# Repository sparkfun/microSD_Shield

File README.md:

SparkFun microSD Shield
===========================

[*microSD Shield (DEV-12761)*](https://www.sparkfun.com/products/12761)

The microSD shield equips your Arduino with mass-storage capability, so you can use it for data-logging or other related projects. 

Repository Contents
-------------------

* **/Firmware** - Example .INO sketch for Arduino. Requires the SD.h library
* **/Hardware** - All Eagle design files (.brd, .sch)
* **/Production** - Test bed files and production panel files

Documentation
--------------
* **[Hookup Guide](https://learn.sparkfun.com/tutorials/microsd-shield-and-sd-breakout-hookup-guide)** - Basic hookup guide for the microSD Shield.
* **[SparkFun Fritzing repo](https://github.com/sparkfun/Fritzing_Parts)** - Fritzing diagrams for SparkFun products.
* **[SparkFun 3D Model repo](https://github.com/sparkfun/3D_Models)** - 3D models of SparkFun products. 

Product Versions
----------------
* [DEV-09802](https://www.sparkfun.com/products/9802)- Hardware version 1.3. Designed for Uno (not R3)

Version History
---------------
* [v1.3](https://github.com/sparkfun/microSD_Shield/tree/V_1.3) Version 1.3

License Information
-------------------

This product is _**open source**_! 

Please review the LICENSE.md file for license information. 

If you have any questions or concerns on licensing, please contact techsupport@sparkfun.com.

Distributed as-is; no warranty is given.

- Your friends at SparkFun.

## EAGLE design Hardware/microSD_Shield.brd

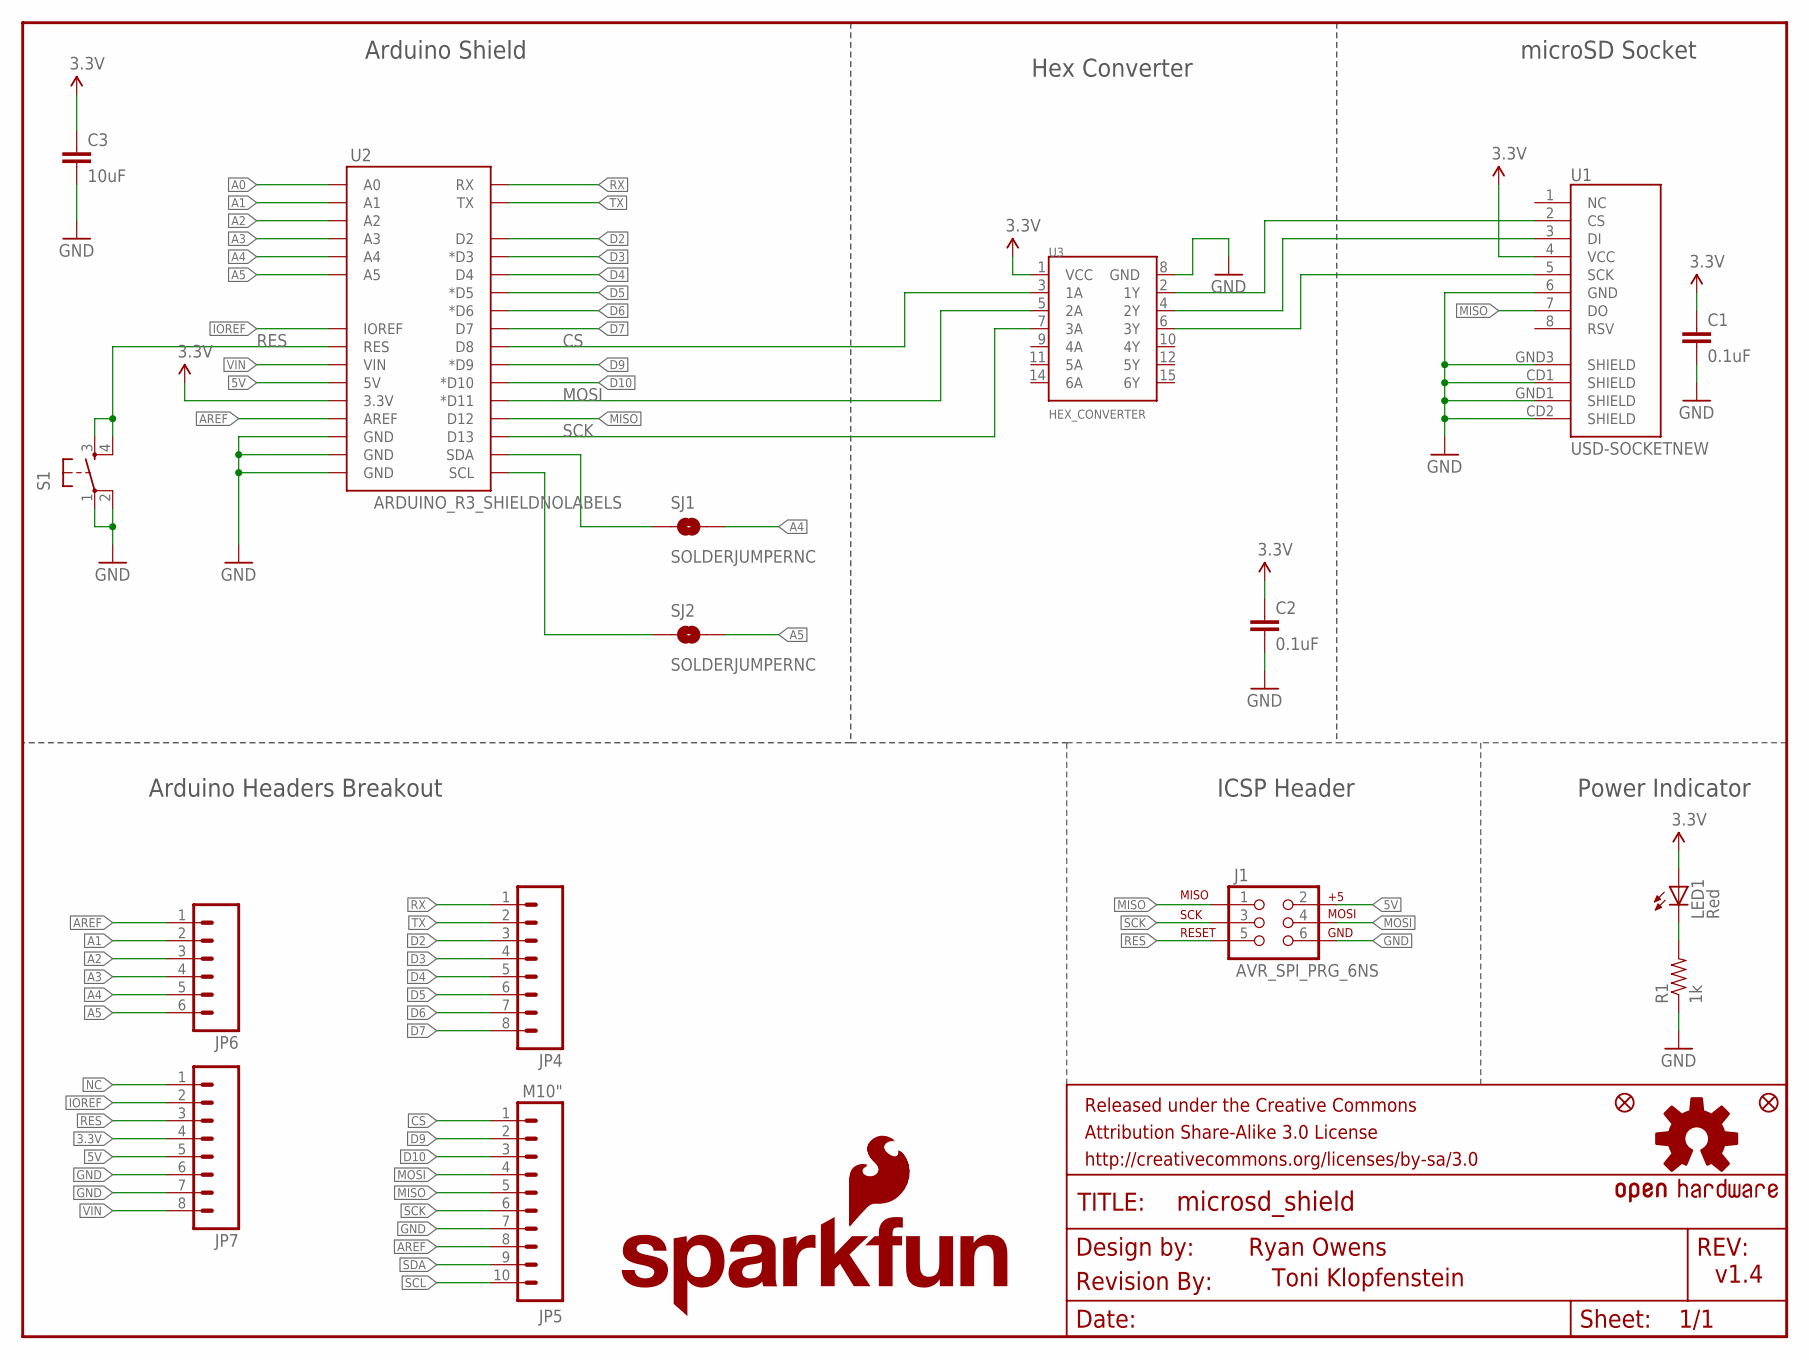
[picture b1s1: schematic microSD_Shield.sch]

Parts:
C1, C2: 0.1uF; 0603-CAP
C3: 10uF; 0603-CAP
FRAME1: FRAME-LETTER; CREATIVE_COMMONS
J1: AVR_SPI_PRG_6NS; 2X3-NS
JP1: SFE_LOGO_NAME_FLAME.1_INCH; SFE_LOGO_NAME_FLAME_.1
JP2, JP3: FIDUCIAL1X2; FIDUCIAL-1X2
JP4: M08; 1X08
JP5: M10"; 1X10
JP6: M06SIP; 1X06
JP7: M081X08; 1X08
LED1: Red; LED-0603
LOGO1: OSHW-LOGOM; OSHW-LOGO-M
LOGO2: SFE_LOGO_FLAME.6_INCH; SFE_LOGO_FLAME_.6
R1: 1k; 0603-RES
S1: TAC_SWITCHSMD; TACTILE_SWITCH_SMD
SJ1, SJ2: SOLDERJUMPERNC; SJ_2S
U1: USD-SOCKETNEW; MICRO-SD-SOCKET-PP
U2: ARDUINO_R3_SHIELDNOLABELS; UNO_R3_SHIELD_NOLABELS
U3: HEX_CONVERTER; SO016
U$1: REVISION

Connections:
3.3V: C1.1, C2.1, C3.1, JP7.4, LED1.A, U1.4 (VCC), U2.3.3V, U3.1 (VCC)
5V: J1.2, JP7.5, U2.5V
A0: JP6.1, U2.A0
A1: JP6.2, U2.A1
A2: JP6.3, U2.A2
A3: JP6.4, U2.A3
A4: JP6.5, SJ1.2, U2.A4
A5: JP6.6, SJ2.2, U2.A5
AREF: JP5.8, U2.AREF
CS: JP5.1, U2.D8, U3.3 (1A)
D2: JP4.3, U2.D2
D3: JP4.4, U2.D3 (*D3)
D4: JP4.5, U2.D4
D5: JP4.6, U2.D5 (*D5)
D6: JP4.7, U2.D6 (*D6)
D7: JP4.8, U2.D7
D9: JP5.2, U2.D9 (*D9)
D10: JP5.3, U2.D10 (*D10)
GND: C1.2, C2.2, C3.2, J1.6, JP5.7, JP7.6, JP7.7, R1.1, S1.1, S1.2, U1.6 (GND), U1.CD1 (SHIELD), U1.CD2 (SHIELD), U1.GND1 (SHIELD), U1.GND3 (SHIELD), U2.GND@0 (GND), U2.GND@1 (GND), U2.GND@2 (GND), U3.8 (GND)
IOREF: JP7.2, U2.IOREF
MISO: J1.1, JP5.5, U1.7 (DO), U2.D12
MOSI: J1.4, JP5.4, U2.D11 (*D11), U3.5 (2A)
unnamed: U1.3 (DI), U3.4 (2Y)
unnamed: U1.5 (SCK), U3.6 (3Y)
unnamed: LED1.C, R1.2
unnamed: U1.2 (CS), U3.2 (1Y)
NC: JP7.1
RES: J1.5, JP7.3, S1.3, S1.4, U2.RES
RX: JP4.1, U2.RX
SCK: J1.3, JP5.6, U2.D13, U3.7 (3A)
SCL: JP5.10, SJ2.1, U2.SCL
SDA: JP5.9, SJ1.1, U2.SDA
TX: JP4.2, U2.TX
VIN: JP7.8, U2.VIN

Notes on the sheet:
Power Indicator
Ryan Owens
v1.4
Toni Klopfenstein
Arduino Headers Breakout
ICSP Header
microSD Socket
Hex Converter
Arduino Shield

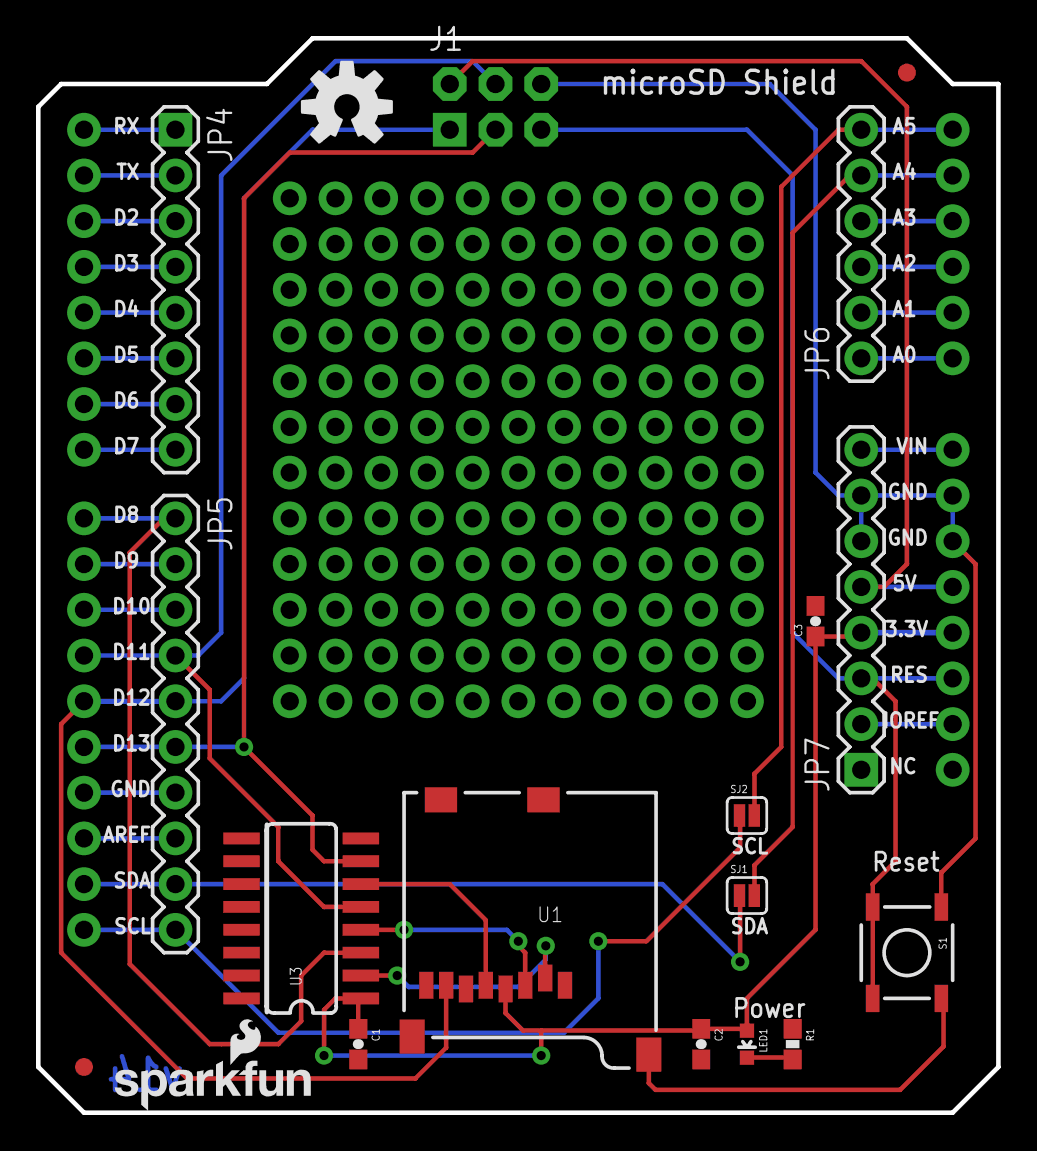
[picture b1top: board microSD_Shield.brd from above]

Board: 2 copper layers, 53.3 x 59.7 mm, 23 parts (1 on the bottom side), 33 nets.

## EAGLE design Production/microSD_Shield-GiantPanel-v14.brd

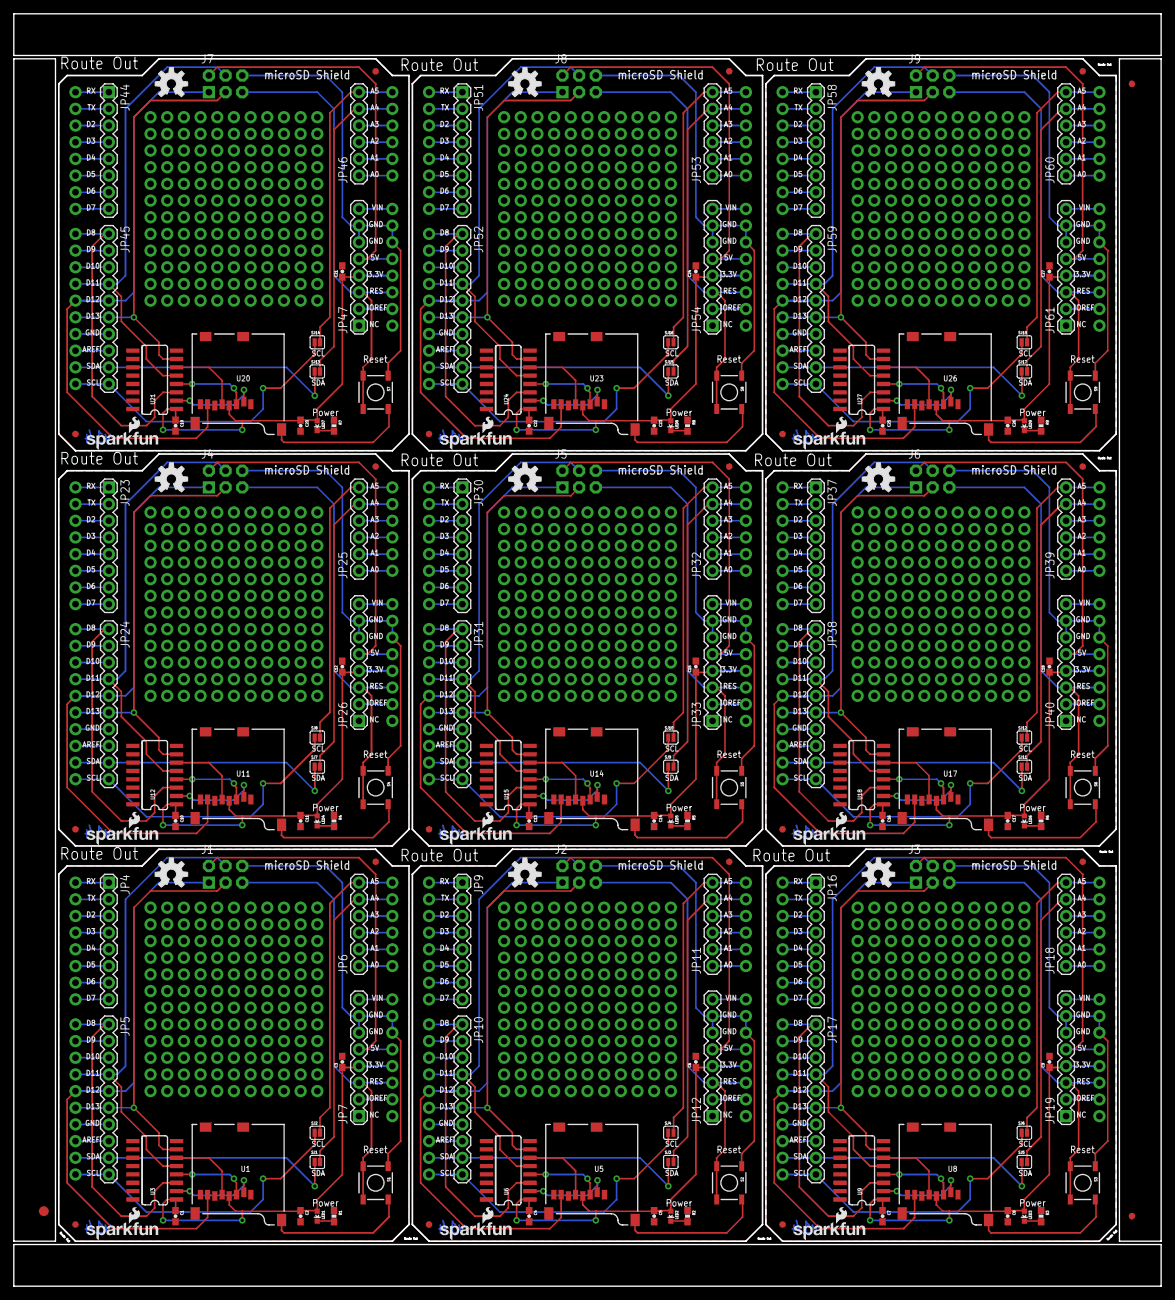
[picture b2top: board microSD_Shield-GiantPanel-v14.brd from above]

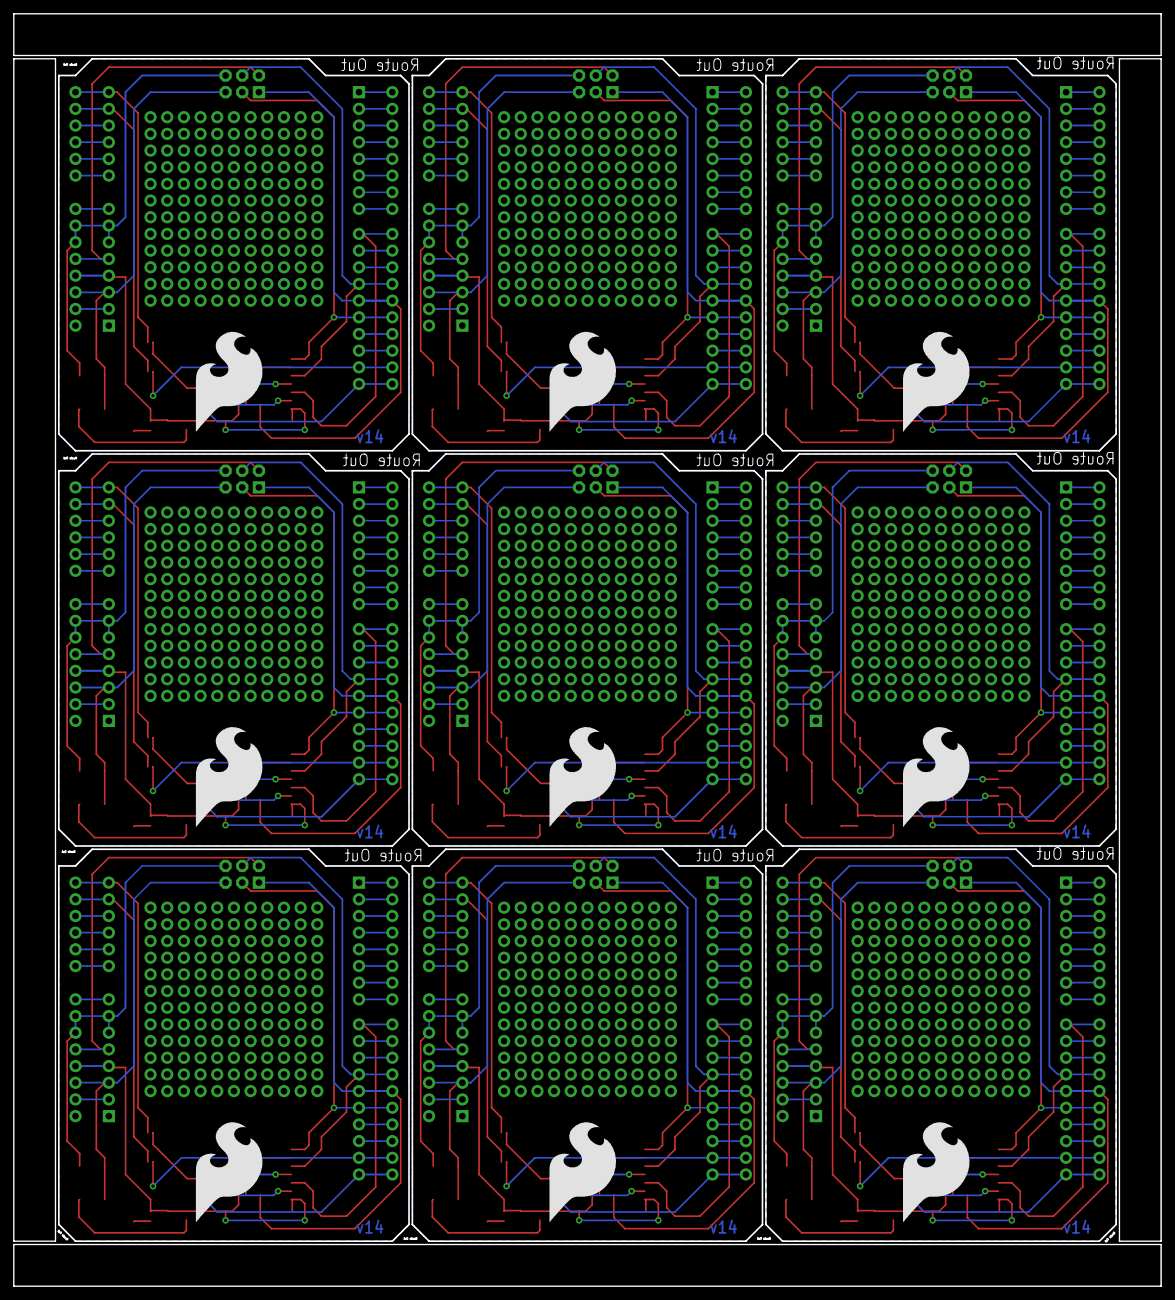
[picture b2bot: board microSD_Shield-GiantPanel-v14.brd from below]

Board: 2 copper layers, 174.8 x 193.8 mm, 192 parts (9 on the bottom side), 297 nets.

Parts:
C1, C2, C4, C5, C7, C8, C10, C11, C13, C14, C16, C17, C19, C20, C22, C23, C25, C26: 0.1uF; 0603-CAP
C3, C6, C9, C12, C15, C18, C21, C24, C27: 10uF; 0603-CAP
E$1: FIDUCIAL-1.5X3
E$6, E$8: FIDUCIAL-1X2
J1, J2, J3, J4, J5, J6, J7, J8, J9: AVR_SPI_PRG_6NS; 2X3-NS
JP1, JP8, JP15, JP22, JP29, JP36, JP43, JP50, JP57: SFE_LOGO_NAME_FLAME.1_INCH; SFE_LOGO_NAME_FLAME_.1
JP2, JP3, JP13, JP14, JP20, JP21, JP27, JP28, JP34, JP35, JP41, JP42, JP48, JP49, JP55, JP56, JP62, JP63: FIDUCIAL1X2; FIDUCIAL-1X2
JP4, JP7, JP9, JP12, JP16, JP19, JP23, JP26, JP30, JP33, JP37, JP40, JP44, JP47, JP51, JP54, JP58, JP61: 1X08
JP5, JP10, JP17, JP24, JP31, JP38, JP45, JP52, JP59: M10"; 1X10
JP6, JP11, JP18, JP25, JP32, JP39, JP46, JP53, JP60: 1X06
LED1, LED2, LED3, LED4, LED5, LED6, LED7, LED8, LED9: Red; LED-0603
LOGO1, LOGO3, LOGO5, LOGO7, LOGO9, LOGO11, LOGO13, LOGO15, LOGO17: OSHW-LOGOM; OSHW-LOGO-M
LOGO2, LOGO4, LOGO6, LOGO8, LOGO10, LOGO12, LOGO14, LOGO16, LOGO18: SFE_LOGO_FLAME.6_INCH; SFE_LOGO_FLAME_.6
R1, R2, R3, R4, R5, R6, R7, R8, R9: 1k; 0603-RES
S1, S2, S3, S4, S5, S6, S7, S8, S9: TACTILE_SWITCH_SMD
SJ1, SJ2, SJ3, SJ4, SJ5, SJ6, SJ7, SJ8, SJ9, SJ10, SJ11, SJ12, SJ13, SJ14, SJ15, SJ16, SJ17, SJ18: SOLDERJUMPERNC; SJ_2S
U1, U5, U8, U11, U14, U17, U20, U23, U26: USD-SOCKETNEW; MICRO-SD-SOCKET-PP
U2, U4, U7, U10, U13, U16, U19, U22, U25: ARDUINO_R3_SHIELDNOLABELS; UNO_R3_SHIELD_NOLABELS
U3, U6, U9, U12, U15, U18, U21, U24, U27: HEX_CONVERTER; SO016

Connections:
3.3V: C1.1, C2.1, C3.1, JP7.4, LED1.A, U1.4, U2.3.3V, U3.1
3.3V1: C4.1, C5.1, C6.1, JP12.4, LED2.A, U4.3.3V, U5.4, U6.1
3.3V2: C7.1, C8.1, C9.1, JP19.4, LED3.A, U7.3.3V, U8.4, U9.1
3.3V3: C10.1, C11.1, C12.1, JP26.4, LED4.A, U10.3.3V, U11.4, U12.1
3.3V4: C13.1, C14.1, C15.1, JP33.4, LED5.A, U13.3.3V, U14.4, U15.1
3.3V5: C16.1, C17.1, C18.1, JP40.4, LED6.A, U16.3.3V, U17.4, U18.1
3.3V6: C19.1, C20.1, C21.1, JP47.4, LED7.A, U19.3.3V, U20.4, U21.1
3.3V7: C22.1, C23.1, C24.1, JP54.4, LED8.A, U22.3.3V, U23.4, U24.1
3.3V8: C25.1, C26.1, C27.1, JP61.4, LED9.A, U25.3.3V, U26.4, U27.1
5V: J1.2, JP7.5, U2.5V
5V1: J2.2, JP12.5, U4.5V
5V2: J3.2, JP19.5, U7.5V
5V3: J4.2, JP26.5, U10.5V
5V4: J5.2, JP33.5, U13.5V
5V5: J6.2, JP40.5, U16.5V
5V6: J7.2, JP47.5, U19.5V
5V7: J8.2, JP54.5, U22.5V
5V8: J9.2, JP61.5, U25.5V
A0: JP6.1, U2.A0
A1: JP6.2, U2.A1
A2: JP6.3, U2.A2
A3: JP6.4, U2.A3
A4: JP6.5, SJ1.2, U2.A4
A5: JP6.6, SJ2.2, U2.A5
A6: JP11.1, U4.A0
A7: JP11.2, U4.A1
A8: JP11.3, U4.A2
A9: JP11.4, U4.A3
A10: JP11.5, SJ3.2, U4.A4
A11: JP11.6, SJ4.2, U4.A5
A12: JP18.1, U7.A0
A13: JP18.2, U7.A1
A14: JP18.3, U7.A2
A15: JP18.4, U7.A3
A16: JP18.5, SJ5.2, U7.A4
A17: JP18.6, SJ6.2, U7.A5
A18: JP25.1, U10.A0
A19: JP25.2, U10.A1
A20: JP25.3, U10.A2
A21: JP25.4, U10.A3
A22: JP25.5, SJ7.2, U10.A4
A23: JP25.6, SJ8.2, U10.A5
A24: JP32.1, U13.A0
A25: JP32.2, U13.A1
A26: JP32.3, U13.A2
A27: JP32.4, U13.A3
A28: JP32.5, SJ9.2, U13.A4
A29: JP32.6, SJ10.2, U13.A5
A30: JP39.1, U16.A0
A31: JP39.2, U16.A1
A32: JP39.3, U16.A2
A33: JP39.4, U16.A3
A34: JP39.5, SJ11.2, U16.A4
A35: JP39.6, SJ12.2, U16.A5
A36: JP46.1, U19.A0
A37: JP46.2, U19.A1
A38: JP46.3, U19.A2
A39: JP46.4, U19.A3
A40: JP46.5, SJ13.2, U19.A4
A41: JP46.6, SJ14.2, U19.A5
A42: JP53.1, U22.A0
A43: JP53.2, U22.A1
A44: JP53.3, U22.A2
A45: JP53.4, U22.A3
A46: JP53.5, SJ15.2, U22.A4
A47: JP53.6, SJ16.2, U22.A5
A48: JP60.1, U25.A0
A49: JP60.2, U25.A1
A50: JP60.3, U25.A2
A51: JP60.4, U25.A3
A52: JP60.5, SJ17.2, U25.A4
A53: JP60.6, SJ18.2, U25.A5
AREF: JP5.8, U2.AREF
AREF1: JP10.8, U4.AREF
AREF2: JP17.8, U7.AREF
AREF3: JP24.8, U10.AREF
AREF4: JP31.8, U13.AREF
AREF5: JP38.8, U16.AREF
AREF6: JP45.8, U19.AREF
AREF7: JP52.8, U22.AREF
AREF8: JP59.8, U25.AREF
CS: JP5.1, U2.D8, U3.3
CS1: JP10.1, U4.D8, U6.3
CS2: JP17.1, U7.D8, U9.3
CS3: JP24.1, U10.D8, U12.3
CS4: JP31.1, U13.D8, U15.3
CS5: JP38.1, U16.D8, U18.3
CS6: JP45.1, U19.D8, U21.3
CS7: JP52.1, U22.D8, U24.3
CS8: JP59.1, U25.D8, U27.3
D1: JP9.3, U4.D2
D2: JP4.3, U2.D2
D3: JP4.4, U2.D3
D4: JP4.5, U2.D4
D5: JP4.6, U2.D5
D6: JP4.7, U2.D6
D7: JP4.8, U2.D7
D8: JP9.4, U4.D3
D9: JP5.2, U2.D9
D10: JP5.3, U2.D10
D11: JP9.5, U4.D4
D12: JP9.6, U4.D5
D13: JP9.7, U4.D6
D14: JP9.8, U4.D7
D15: JP10.2, U4.D9
D16: JP10.3, U4.D10
D17: JP16.3, U7.D2
D18: JP16.4, U7.D3
D19: JP16.5, U7.D4
D20: JP16.6, U7.D5
D21: JP16.7, U7.D6
D22: JP16.8, U7.D7
D23: JP17.2, U7.D9
D24: JP17.3, U7.D10
D25: JP23.3, U10.D2
D26: JP23.4, U10.D3
D27: JP23.5, U10.D4
D28: JP23.6, U10.D5
D29: JP23.7, U10.D6
D30: JP23.8, U10.D7
D31: JP24.2, U10.D9
D32: JP24.3, U10.D10
D33: JP30.3, U13.D2
D34: JP30.4, U13.D3
D35: JP30.5, U13.D4
D36: JP30.6, U13.D5
D37: JP30.7, U13.D6
D38: JP30.8, U13.D7
D39: JP31.2, U13.D9
D40: JP31.3, U13.D10
D41: JP37.3, U16.D2
D42: JP37.4, U16.D3
D43: JP37.5, U16.D4
D44: JP37.6, U16.D5
D45: JP37.7, U16.D6
D46: JP37.8, U16.D7
D47: JP38.2, U16.D9
D48: JP38.3, U16.D10
D49: JP44.3, U19.D2
D50: JP44.4, U19.D3
D51: JP44.5, U19.D4
D52: JP44.6, U19.D5
D53: JP44.7, U19.D6
D54: JP44.8, U19.D7
D55: JP45.2, U19.D9
D56: JP45.3, U19.D10
D57: JP51.3, U22.D2
D58: JP51.4, U22.D3
D59: JP51.5, U22.D4
D60: JP51.6, U22.D5
D61: JP51.7, U22.D6
D62: JP51.8, U22.D7
D63: JP52.2, U22.D9
D64: JP52.3, U22.D10
D65: JP58.3, U25.D2
D66: JP58.4, U25.D3
D67: JP58.5, U25.D4
D68: JP58.6, U25.D5
D69: JP58.7, U25.D6
D70: JP58.8, U25.D7
D71: JP59.2, U25.D9
D72: JP59.3, U25.D10
GND: C1.2, C2.2, C3.2, J1.6, JP5.7, JP7.6, JP7.7, R1.1, S1.1, S1.2, U1.6, U1.CD1, U1.CD2, U1.GND1, U1.GND3, U2.GND@0, U2.GND@1, U2.GND@2, U3.8
GND1: C4.2, C5.2, C6.2, J2.6, JP10.7, JP12.6, JP12.7, R2.1, S2.1, S2.2, U4.GND@0, U4.GND@1, U4.GND@2, U5.6, U5.CD1, U5.CD2, U5.GND1, U5.GND3, U6.8
GND2: C7.2, C8.2, C9.2, J3.6, JP17.7, JP19.6, JP19.7, R3.1, S3.1, S3.2, U7.GND@0, U7.GND@1, U7.GND@2, U8.6, U8.CD1, U8.CD2, U8.GND1, U8.GND3, U9.8
GND3: C10.2, C11.2, C12.2, J4.6, JP24.7, JP26.6, JP26.7, R4.1, S4.1, S4.2, U10.GND@0, U10.GND@1, U10.GND@2, U11.6, U11.CD1, U11.CD2, U11.GND1, U11.GND3, U12.8
GND4: C13.2, C14.2, C15.2, J5.6, JP31.7, JP33.6, JP33.7, R5.1, S5.1, S5.2, U13.GND@0, U13.GND@1, U13.GND@2, U14.6, U14.CD1, U14.CD2, U14.GND1, U14.GND3, U15.8
GND5: C16.2, C17.2, C18.2, J6.6, JP38.7, JP40.6, JP40.7, R6.1, S6.1, S6.2, U16.GND@0, U16.GND@1, U16.GND@2, U17.6, U17.CD1, U17.CD2, U17.GND1, U17.GND3, U18.8
GND6: C19.2, C20.2, C21.2, J7.6, JP45.7, JP47.6, JP47.7, R7.1, S7.1, S7.2, U19.GND@0, U19.GND@1, U19.GND@2, U20.6, U20.CD1, U20.CD2, U20.GND1, U20.GND3, U21.8
GND7: C22.2, C23.2, C24.2, J8.6, JP52.7, JP54.6, JP54.7, R8.1, S8.1, S8.2, U22.GND@0, U22.GND@1, U22.GND@2, U23.6, U23.CD1, U23.CD2, U23.GND1, U23.GND3, U24.8
GND8: C25.2, C26.2, C27.2, J9.6, JP59.7, JP61.6, JP61.7, R9.1, S9.1, S9.2, U25.GND@0, U25.GND@1, U25.GND@2, U26.6, U26.CD1, U26.CD2, U26.GND1, U26.GND3, U27.8
IOREF: JP7.2, U2.IOREF
IOREF1: JP12.2, U4.IOREF
IOREF2: JP19.2, U7.IOREF
IOREF3: JP26.2, U10.IOREF
IOREF4: JP33.2, U13.IOREF
IOREF5: JP40.2, U16.IOREF
IOREF6: JP47.2, U19.IOREF
IOREF7: JP54.2, U22.IOREF
IOREF8: JP61.2, U25.IOREF
MISO: J1.1, JP5.5, U1.7, U2.D12
MISO1: J2.1, JP10.5, U4.D12, U5.7
MISO2: J3.1, JP17.5, U7.D12, U8.7
MISO3: J4.1, JP24.5, U10.D12, U11.7
MISO4: J5.1, JP31.5, U13.D12, U14.7
MISO5: J6.1, JP38.5, U16.D12, U17.7
MISO6: J7.1, JP45.5, U19.D12, U20.7
MISO7: J8.1, JP52.5, U22.D12, U23.7
MISO8: J9.1, JP59.5, U25.D12, U26.7
MOSI: J1.4, JP5.4, U2.D11, U3.5
MOSI1: J2.4, JP10.4, U4.D11, U6.5
MOSI2: J3.4, JP17.4, U7.D11, U9.5
MOSI3: J4.4, JP24.4, U10.D11, U12.5
MOSI4: J5.4, JP31.4, U13.D11, U15.5
MOSI5: J6.4, JP38.4, U16.D11, U18.5
MOSI6: J7.4, JP45.4, U19.D11, U21.5
MOSI7: J8.4, JP52.4, U22.D11, U24.5
MOSI8: J9.4, JP59.4, U25.D11, U27.5
unnamed: U5.3, U6.4
unnamed: U1.3, U3.4
unnamed: LED2.C, R2.2
unnamed: U1.5, U3.6
unnamed: LED1.C, R1.2
unnamed: U1.2, U3.2
unnamed: U5.2, U6.2
unnamed: U5.5, U6.6
unnamed: U8.3, U9.4
unnamed: LED3.C, R3.2
unnamed: U8.2, U9.2
unnamed: U8.5, U9.6
unnamed: U11.3, U12.4
unnamed: LED4.C, R4.2
unnamed: U11.2, U12.2
unnamed: U11.5, U12.6
unnamed: U14.3, U15.4
unnamed: LED5.C, R5.2
unnamed: U14.2, U15.2
unnamed: U14.5, U15.6
unnamed: U17.3, U18.4
unnamed: LED6.C, R6.2
unnamed: U17.2, U18.2
unnamed: U17.5, U18.6
unnamed: U20.3, U21.4
unnamed: LED7.C, R7.2
unnamed: U20.2, U21.2
unnamed: U20.5, U21.6
unnamed: U23.3, U24.4
unnamed: LED8.C, R8.2
unnamed: U23.2, U24.2
unnamed: U23.5, U24.6
unnamed: U26.3, U27.4
unnamed: LED9.C, R9.2
unnamed: U26.2, U27.2
unnamed: U26.5, U27.6
RES: J1.5, JP7.3, S1.3, S1.4, U2.RES
RES1: J2.5, JP12.3, S2.3, S2.4, U4.RES
RES2: J3.5, JP19.3, S3.3, S3.4, U7.RES
RES3: J4.5, JP26.3, S4.3, S4.4, U10.RES
RES4: J5.5, JP33.3, S5.3, S5.4, U13.RES
RES5: J6.5, JP40.3, S6.3, S6.4, U16.RES
RES6: J7.5, JP47.3, S7.3, S7.4, U19.RES
RES7: J8.5, JP54.3, S8.3, S8.4, U22.RES
RES8: J9.5, JP61.3, S9.3, S9.4, U25.RES
RX: JP4.1, U2.RX
RX1: JP9.1, U4.RX
RX2: JP16.1, U7.RX
RX3: JP23.1, U10.RX
RX4: JP30.1, U13.RX
RX5: JP37.1, U16.RX
RX6: JP44.1, U19.RX
RX7: JP51.1, U22.RX
RX8: JP58.1, U25.RX
SCK: J1.3, JP5.6, U2.D13, U3.7
SCK1: J2.3, JP10.6, U4.D13, U6.7
SCK2: J3.3, JP17.6, U7.D13, U9.7
SCK3: J4.3, JP24.6, U10.D13, U12.7
SCK4: J5.3, JP31.6, U13.D13, U15.7
SCK5: J6.3, JP38.6, U16.D13, U18.7
SCK6: J7.3, JP45.6, U19.D13, U21.7
SCK7: J8.3, JP52.6, U22.D13, U24.7
SCK8: J9.3, JP59.6, U25.D13, U27.7
SCL: JP5.10, SJ2.1, U2.SCL
SCL1: JP10.10, SJ4.1, U4.SCL
SCL2: JP17.10, SJ6.1, U7.SCL
SCL3: JP24.10, SJ8.1, U10.SCL
SCL4: JP31.10, SJ10.1, U13.SCL
SCL5: JP38.10, SJ12.1, U16.SCL
SCL6: JP45.10, SJ14.1, U19.SCL
SCL7: JP52.10, SJ16.1, U22.SCL
SCL8: JP59.10, SJ18.1, U25.SCL
SDA: JP5.9, SJ1.1, U2.SDA
SDA1: JP10.9, SJ3.1, U4.SDA
SDA2: JP17.9, SJ5.1, U7.SDA
SDA3: JP24.9, SJ7.1, U10.SDA
SDA4: JP31.9, SJ9.1, U13.SDA
SDA5: JP38.9, SJ11.1, U16.SDA
SDA6: JP45.9, SJ13.1, U19.SDA
SDA7: JP52.9, SJ15.1, U22.SDA
SDA8: JP59.9, SJ17.1, U25.SDA
TX: JP4.2, U2.TX
TX1: JP9.2, U4.TX
TX2: JP16.2, U7.TX
TX3: JP23.2, U10.TX
TX4: JP30.2, U13.TX
TX5: JP37.2, U16.TX
TX6: JP44.2, U19.TX
TX7: JP51.2, U22.TX
TX8: JP58.2, U25.TX
VIN: JP7.8, U2.VIN
VIN1: JP12.8, U4.VIN
VIN2: JP19.8, U7.VIN
VIN3: JP26.8, U10.VIN
VIN4: JP33.8, U13.VIN
VIN5: JP40.8, U16.VIN
VIN6: JP47.8, U19.VIN
VIN7: JP54.8, U22.VIN
VIN8: JP61.8, U25.VIN

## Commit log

2014-02-11 Initial board file commit
2014-02-12 Adding v1.4 board files
2014-02-25 Adding decoupling capacitors
2014-02-28 Adding bottom flame to pcb
2014-04-17 Upping back flame size
2014-04-18 created giant panel v14
2014-09-18 Firmware Update for SD_Datalogger.ino
    1.) Missing a line to create a string so the sketch won't compile in Arduino.
    2.) Added links the original example code from Arduino and SD library on GitHub by William Greiman.
    3.) Includes some outputs to the Serial Monitor for debugging.
2014-10-17 Updating README to new product links
2015-06-26 Various fixes
    Updated description to correct CS pin used in example
    Added include for SPI.h which is required to compile
    Removed unused String and all references thereto
    Fixed incorrect casting of millis() to int, which was causing rollover
    after 37 seconds
    Added label to timestamp serial output for consistency with file
2015-06-29 Fixing directory name, adding license file, updating README

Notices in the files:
parts and their libraries:
SparkFun-Aesthetics: Licensing: CC v3.0 Share-Alike You are welcome to use this library for commercial purposes.
SparkFun-Aesthetics: Released under the Creative Commons Attribution Share-Alike 3.0 License
SparkFun-Aesthetics: http://creativecommons.org/licenses/by-sa/3.0
